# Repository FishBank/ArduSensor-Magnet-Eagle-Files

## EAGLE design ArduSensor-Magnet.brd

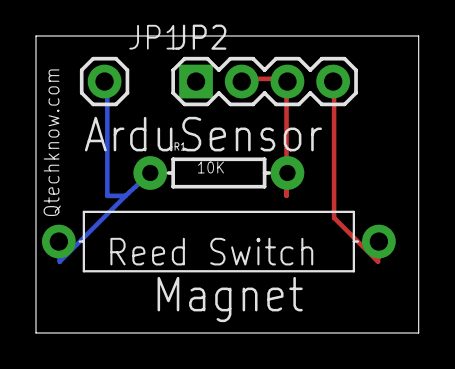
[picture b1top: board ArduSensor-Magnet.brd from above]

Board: 2 copper layers, 21.3 x 16.5 mm, 4 parts (0 on the bottom side), 3 nets.

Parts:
JP1: M01PTH; 1X01
JP2: 1X04
R1: AXIAL-0.3
S1: SWITCH-MOMENTARY-2PTH_REED2; REED_SWITCH_PLASTIC

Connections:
unnamed: JP1.1, R1.P$1, S1.P$1
unnamed: JP2.2, JP2.3, R1.P$2
unnamed: JP2.4, S1.P$2

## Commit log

2012-07-13 Schematic

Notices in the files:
parts and their libraries:
SFE Connectors: Licensing: CC v3.0 Share-Alike You are welcome to use this library for commercial purposes.
